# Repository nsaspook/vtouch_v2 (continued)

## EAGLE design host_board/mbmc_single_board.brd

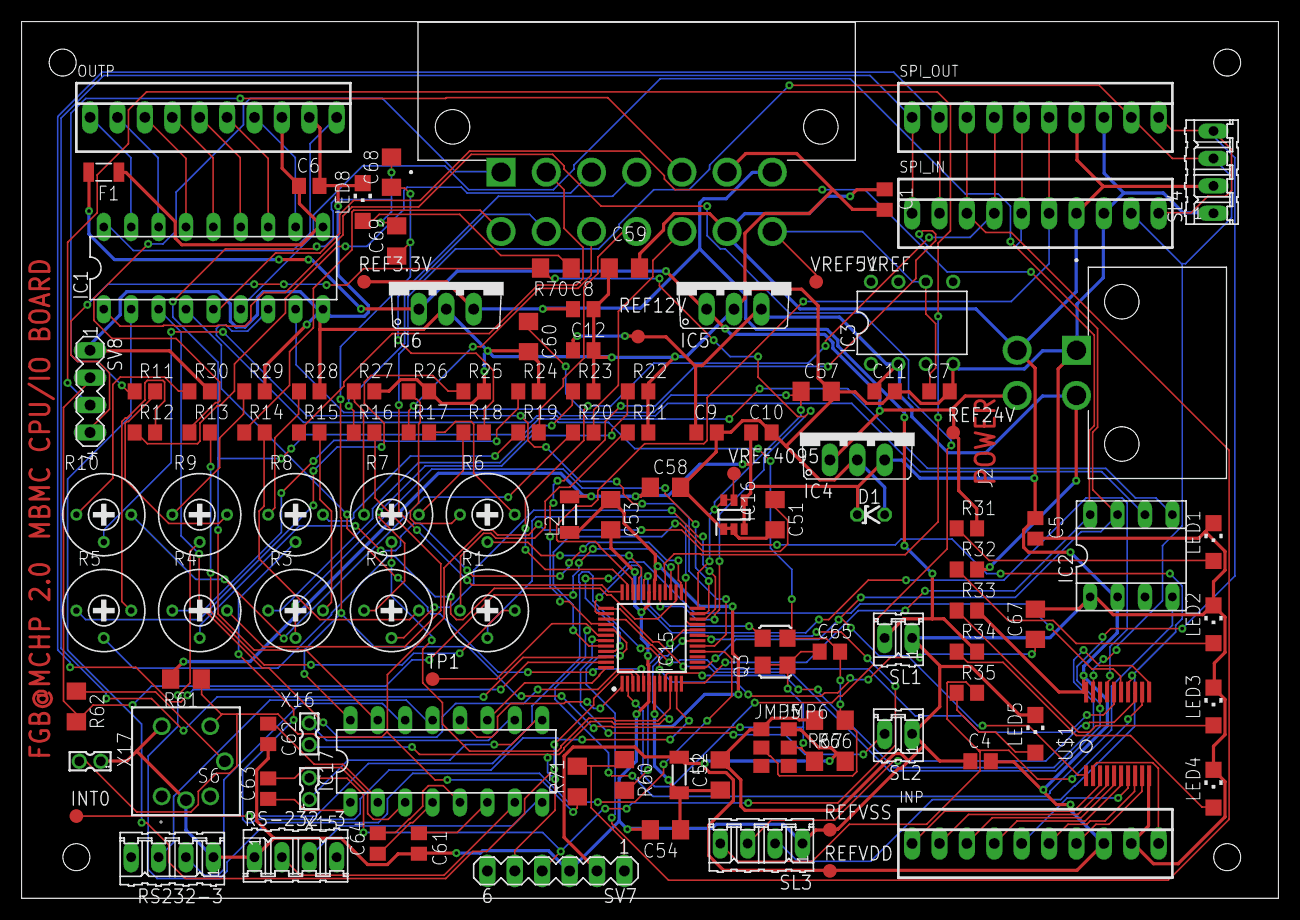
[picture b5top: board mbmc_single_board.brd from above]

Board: 2 copper layers, 116.5 x 81.3 mm, 118 parts (0 on the bottom side), 123 nets.

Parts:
C1, C12: 22uf; C0805
C4, C5, C6, C7, C8, C9, C10, C11: 0.1; C0805
C51, C52, C53, C57, C58, C67, C68, C69: 0.1; C1206
C54, C59, C60: 15uf; C1206
C61, C62, C63, C64, C65: 1uf; C0805
D1: 5.6v; ZDIO-2.5
F1: 1206L050; 1206L
IC1: ULN2803; DIL18
IC2: DIP Socket; SOCKET-08
IC3: REF02 5 VOLTS; DIL08
IC4: 5 VOLTS; TO220V
IC5: 12 VOLTS; TO220V
IC6: 3.3 VOLTS; TO220V
IC15: PIC18F57K42-E_PT; QFP50P900X900X120-48N
IC16: REF3440IDBVR; SOP95P280X145-6N
IC17: MAX232; DIL16
INP: 22-23-2101
INT0: TPB1,27; B1,27
J1: 1-1586043-4; TE_1-1586043-4
J2: 1586044-4; TE_1586044-4
JMP5, JMP6: 0R-JUMPA; A0R-JMP
L1, L2: 1000; SM-1206
LED1: 24 on; CHIPLED_1206
LED2: 12 on; CHIPLED_1206
LED3: 5 on; CHIPLED_1206
LED4: 3.3 on; CHIPLED_1206
LED5: debug8; CHIPLED_1206
LED8: DBLED; CHIPLED_1206
OUTP: 22-23-2101
Q3: ASF1; ASF
R1, R2, R3, R4, R5, R6, R7, R8, R9, R10: 200; RTRIM3339P
R11, R15, R16, R17, R18: 9.85k; R0805
R12, R20: 21.5k; R0805
R13, R14, R19: 811; R0805
R21, R22, R28: 3820; R0805
R23, R24, R25, R26, R27, R29, R30: 1.28k; R0805
R31: 10k; R0805
R32: 5k; R0805
R33, R34, R35: 1k; R0805
R60, R62, R70, R71: 220; R1206
R61: 10000; R1206
R66, R67: 0; R1206
REF3.3V, REF12V, REF24V: TPB1,27; B1,27
REFVDD: TPB1,27; B1,27
REFVSS: TPB1,27; B1,27
RS232-3: serial1; 04P
RS-232-3: serial2; 04P
S6: RESET SW; B3W-9_1-LED
SL1: 3.3 GLORY; 02P
SL2: PWM; 02P
SL3: MISC INP; 04P
SL4: SPI SEL; 04P
SPI_IN: 22-23-2101
SPI_OUT: 22-23-2101
SV7: ICSP; MA06-1
SV8: DEBUG; MA04-1
TP1: TPB1,27; B1,27
U$1: MAX6818; SSOP20
VREF5VREF, VREF4095: TPB1,27; B1,27
X15: RX-2; 332-02
X16: TX-2; 332-02
X17: RESETJMP; 332-02

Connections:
+3V3: C8.1, IC6.3, J1.13, R34.2, REF3.3V.TP, SL1.2
+12V: C9.1, C11.1, C12.1, IC3.2, IC5.3, J2.3, R32.2, REF12V.TP
+24V: F1.2, IC4.1, IC5.1, IC6.1, J2.4, R31.2, REF24V.TP
GND: C65.2, C68.2, C69.2, IC17.15, JMP5.2, Q3.2, R67.1
unnamed: R9.3, R11.2
unnamed: R5.3, R12.2
unnamed: R1.3, R13.2
unnamed: R2.3, R14.2
unnamed: R3.3, R15.2
unnamed: R4.3, R16.2
unnamed: R6.3, R17.2
unnamed: J1.7, R18.2
unnamed: R8.3, R19.1
unnamed: J1.8, R19.2
unnamed: R1.1, R21.1
unnamed: R2.1, R22.1
unnamed: R3.1, R23.1
unnamed: R4.1, R24.1
unnamed: R5.1, R25.1
unnamed: R6.1, R26.1
unnamed: R7.1, R27.1
unnamed: R8.1, R28.1
unnamed: R9.1, R29.1
unnamed: R10.1, R30.1
unnamed: C6.1, F1.1, IC1.10, OUTP.8
unnamed: C52.1, C53.1, C54.1, IC15.7, IC15.30, L1.2, L2.1
unnamed: J1.2, R14.1
unnamed: IC1.7, IC2.5
unnamed: IC1.8, IC2.6
unnamed: IC15.36, SL4.3, SPI_IN.9, SPI_OUT.9, U$1.OUT1
unnamed: INP.10, U$1.IN1
unnamed: INP.1, U$1.IN2
unnamed: INP.2, U$1.IN3
unnamed: INP.3, U$1.IN4
unnamed: INP.4, U$1.IN5
unnamed: INP.5, U$1.IN6
unnamed: INP.6, U$1.IN7
unnamed: INP.7, U$1.IN8
unnamed: IC1.18, OUTP.10
unnamed: IC1.17, OUTP.1
unnamed: IC1.16, OUTP.2
unnamed: IC1.15, OUTP.3
unnamed: IC1.14, OUTP.4
unnamed: IC1.13, OUTP.5
unnamed: IC1.12, OUTP.6
unnamed: IC1.11, OUTP.7
unnamed: C7.1, IC3.6, J1.14, VREF5VREF.TP
unnamed: IC15.46, SPI_IN.1, SPI_OUT.1
unnamed: J1.4, R16.1
unnamed: J1.9, R11.1
unnamed: J1.3, R15.1
unnamed: J1.10, R20.2
unnamed: J1.5, R12.1
unnamed: J1.6, R17.1
unnamed: J1.1, R13.1
unnamed: LED1.A, R31.1
unnamed: LED2.A, R32.1
unnamed: LED3.A, R33.1
unnamed: LED4.A, R34.1
unnamed: LED5.A, R35.1
unnamed: R35.2, SL3.4, U$1.OUT8
unnamed: R10.3, R20.1
unnamed: SL3.3, U$1.OUT7
unnamed: R7.3, R18.1
unnamed: IC17.8, RS-232-3.3
unnamed: IC17.14, RS232-3.2
unnamed: IC15.20, R60.2
unnamed: IC15.19, SV7.4, X15.2
unnamed: IC15.18, SV7.5, X16.2
unnamed: IC15.32, Q3.3
unnamed: C57.1, C60.1, IC15.24, IC16.5, IC16.6, VREF4095.TP
unnamed: C61.1, IC17.6
unnamed: C62.1, IC17.2
unnamed: C63.1, IC17.1
unnamed: C64.1, IC17.4
unnamed: C64.2, IC17.5
unnamed: C63.2, IC17.3
unnamed: IC17.7, RS-232-3.2
unnamed: IC17.13, RS232-3.3
unnamed: IC15.1, IC17.12
unnamed: IC17.9, X15.1
unnamed: IC15.48, IC17.11
unnamed: IC17.10, X16.1
unnamed: R62.1, S6.5
unnamed: IC15.27, R62.2, SV8.2
unnamed: IC15.28, SV8.3
unnamed: IC15.29, R70.2, SV8.4
unnamed: IC2.4, IC15.42, TP1.TP
unnamed: IC15.47, SPI_IN.2, SPI_OUT.2
unnamed: IC15.41, SPI_IN.3, SPI_OUT.3
unnamed: IC15.35, SPI_IN.4, SPI_OUT.4
unnamed: IC15.40, SPI_IN.5, SPI_OUT.5
unnamed: IC15.34, SPI_IN.6, SPI_OUT.6
unnamed: IC15.26, R5.2
unnamed: IC15.25, R4.2
unnamed: IC15.23, R3.2
unnamed: IC15.22, R2.2
unnamed: IC15.21, R1.2
unnamed: IC15.33, R6.2
unnamed: IC15.37, SL4.4, SPI_IN.10, SPI_OUT.10, U$1.OUT2
unnamed: IC15.44, SL3.2, U$1.OUT6
unnamed: IC15.45, U$1.OUT5
unnamed: IC1.1, IC15.2
unnamed: IC1.2, IC15.3
unnamed: IC1.3, IC15.4
unnamed: IC1.4, IC15.5
unnamed: IC15.38, U$1.OUT3
unnamed: IC15.39, U$1.OUT4
unnamed: IC15.43, SL2.2
unnamed: IC15.9, U$1.CH_L
unnamed: IC15.10, R7.2
unnamed: IC15.16, R9.2
unnamed: IC15.17, R10.2
unnamed: IC1.5, IC2.8, IC15.12
unnamed: IC1.6, IC2.7, IC15.13, U$1.EN_L
unnamed: IC15.11, R8.2
unnamed: C67.1, IC15.8, INT0.TP
unnamed: LED8.A, R70.1
unnamed: C51.1, R61.1, R71.1, S6.4, X17.2
unnamed: R60.1, R71.2, SV7.1
VCC: C65.1, C68.1, C69.1, IC17.16, JMP6.2, Q3.1, Q3.4, R66.1
VDD: C1.1, C4.2, C5.1, C10.1, C58.1, C59.1, D1.C, IC2.2, IC4.3, IC16.3, IC16.4, INP.8, J1.12, J2.2, JMP6.1, L1.1, L2.2, R33.2, R61.2, R66.2, REFVDD.TP, SL4.2, SPI_IN.7, SPI_OUT.7, SV7.2, U$1.VCC
VSS: C1.2, C4.1, C5.2, C6.2, C7.2, C8.2, C9.2, C10.2, C11.2, C12.2, C51.2, C52.2, C53.2, C54.2, C57.2, C58.2, C59.2, C60.2, C61.2, C62.2, C67.2, D1.A, IC1.9, IC2.1, IC3.4, IC4.2, IC5.2, IC6.2, IC15.6, IC15.31, IC16.1, IC16.2, INP.9, J1.11, J2.1, JMP5.1, LED1.C, LED2.C, LED3.C, LED4.C, LED5.C, LED8.C, OUTP.9, R21.2, R22.2, R23.2, R24.2, R25.2, R26.2, R27.2, R28.2, R29.2, R30.2, R67.2, REFVSS.TP, RS232-3.1, RS-232-3.1, S6.2, S6.6, SL1.1, SL2.1, SL3.1, SL4.1, SPI_IN.8, SPI_OUT.8, SV7.3, SV8.1, U$1.GND, X17.1

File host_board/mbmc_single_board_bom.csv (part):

"Part";"Value";"Device";"Package";"Description";"ALLIED_NUMBER";"ALLIED_PRICE-STOCK";"AVAILABILITY";"DESCRIPTION";"HEIGHT";"MANUFACTURER";"MANUFACTURER_NAME";"MANUFACTURER_PART_NUMBER";"MF";"MOUSER_PART_NUMBER";"MOUSER_PRICE-STOCK";"MP";"MPN";"OC_FARNELL";"OC_NEWARK";"PACKAGE";"PARTREV";"POPULARITY";"PRICE";"RS_PART_NUMBER";"RS_PRICE-STOCK";"SPICEMODEL";"SPICEPREFIX";"SPICEPREFIXL";"STANDARD";"TP_SIGNAL_NAME";
"C1";"22uf";"C-USC0805";"C0805";"CAPACITOR, American symbol";"";"";"";"";"";"";"";"";"";"";"";"";"";"";"";"";"";"";"";"";"";"";"C";"";"";"";
"C4";"0.1";"C-USC0805";"C0805";"CAPACITOR, American symbol";"";"";"";"";"";"";"";"";"";"";"";"";"";"";"";"";"";"";"";"";"";"";"C";"";"";"";
"C5";"0.1";"C-USC0805";"C0805";"CAPACITOR, American symbol";"";"";"";"";"";"";"";"";"";"";"";"";"";"";"";"";"";"";"";"";"";"";"C";"";"";"";
"C6";"0.1";"C-USC0805";"C0805";"CAPACITOR, American symbol";"";"";"";"";"";"";"";"";"";"";"";"";"";"";"";"";"";"";"";"";"";"";"C";"";"";"";
"C7";"0.1";"C-USC0805";"C0805";"CAPACITOR, American symbol";"";"";"";"";"";"";"";"";"";"";"";"";"";"";"";"";"";"";"";"";"";"";"C";"";"";"";
"C8";"0.1";"C-USC0805";"C0805";"CAPACITOR, American symbol";"";"";"";"";"";"";"";"";"";"";"";"";"";"";"";"";"";"";"";"";"";"";"C";"";"";"";
"C9";"0.1";"C-USC0805";"C0805";"CAPACITOR, American symbol";"";"";"";"";"";"";"";"";"";"";"";"";"";"";"";"";"";"";"";"";"";"";"C";"";"";"";
"C10";"0.1";"C-USC0805";"C0805";"CAPACITOR, American symbol";"";"";"";"";"";"";"";"";"";"";"";"";"";"";"";"";"";"";"";"";"";"";"C";"";"";"";
"C11";"0.1";"C-USC0805";"C0805";"CAPACITOR, American symbol";"";"";"";"";"";"";"";"";"";"";"";"";"";"";"";"";"";"";"";"";"";"";"C";"";"";"";
"C12";"22uf";"C-USC0805";"C0805";"CAPACITOR, American symbol";"";"";"";"";"";"";"";"";"";"";"";"";"";"";"";"";"";"";"";"";"";"";"C";"";"";"";
"C51";"0.1";"C-USC1206";"C1206";"CAPACITOR, American symbol";"";"";"";"";"";"";"";"";"";"";"";"";"";"";"";"";"";"";"";"";"";"";"C";"";"";"";
"C52";"0.1";"C-USC1206";"C1206";"CAPACITOR, American symbol";"";"";"";"";"";"";"";"";"";"";"";"";"";"";"";"";"";"";"";"";"";"";"C";"";"";"";
"C53";"0.1";"C-USC1206";"C1206";"CAPACITOR, American symbol";"";"";"";"";"";"";"";"";"";"";"";"";"";"";"";"";"";"";"";"";"";"";"C";"";"";"";
"C54";"15uf";"C-USC1206";"C1206";"CAPACITOR, American symbol";"";"";"";"";"";"";"";"";"";"";"";"";"";"";"";"";"";"";"";"";"";"";"C";"";"";"";
"C57";"0.1";"C-USC1206";"C1206";"CAPACITOR, American symbol";"";"";"";"";"";"";"";"";"";"";"";"";"";"";"";"";"";"";"";"";"";"";"C";"";"";"";
"C58";"0.1";"C-USC1206";"C1206";"CAPACITOR, American symbol";"";"";"";"";"";"";"";"";"";"";"";"";"";"";"";"";"";"";"";"";"";"";"C";"";"";"";
"C59";"15uf";"C-USC1206";"C1206";"CAPACITOR, American symbol";"";"";"";"";"";"";"";"";"";"";"";"";"";"";"";"";"";"";"";"";"";"";"C";"";"";"";
"C60";"15uf";"C-USC1206";"C1206";"CAPACITOR, American symbol";"";"";"";"";"";"";"";"";"";"";"";"";"";"";"";"";"";"";"";"";"";"";"C";"";"";"";
"C61";"1uf";"C-USC0805";"C0805";"CAPACITOR, American symbol";"";"";"";"";"";"";"";"";"";"";"";"";"";"";"";"";"";"";"";"";"";"";"C";"";"";"";
"C62";"1uf";"C-USC0805";"C0805";"CAPACITOR, American symbol";"";"";"";"";"";"";"";"";"";"";"";"";"";"";"";"";"";"";"";"";"";"";"C";"";"";"";
"C63";"1uf";"C-USC0805";"C0805";"CAPACITOR, American symbol";"";"";"";"";"";"";"";"";"";"";"";"";"";"";"";"";"";"";"";"";"";"";"C";"";"";"";
"C64";"1uf";"C-USC0805";"C0805";"CAPACITOR, American symbol";"";"";"";"";"";"";"";"";"";"";"";"";"";"";"";"";"";"";"";"";"";"";"C";"";"";"";
"C65";"1uf";"C-USC0805";"C0805";"CAPACITOR, American symbol";"";"";"";"";"";"";"";"";"";"";"";"";"";"";"";"";"";"";"";"";"";"";"C";"";"";"";
"C67";"0.1";"C-USC1206";"C1206";"CAPACITOR, American symbol";"";"";"";"";"";"";"";"";"";"";"";"";"";"";"";"";"";"";"";"";"";"";"C";"";"";"";
"C68";"0.1";"C-USC1206";"C1206";"CAPACITOR, American symbol";"";"";"";"";"";"";"";"";"";"";"";"";"";"";"";"";"";"";"";"";"";"";"C";"";"";"";
"C69";"0.1";"C-USC1206";"C1206";"CAPACITOR, American symbol";"";"";"";"";"";"";"";"";"";"";"";"";"";"";"";"";"";"";"";"";"";"";"C";"";"";"";
"D1";"5.6v";"ZENER-DIODEZD-2.5";"ZDIO-2.5";"Z-Diode";"";"";"";"";"";"";"";"";"";"";"";"";"";"";"";"";"";"4";"";"";"";"";"";"";"";"";
"F1";"1206L050";"1206L050";"1206L";"Polyfuse Resettable PTC";"";"";"";"";"";"";"";"";"Littelfuse";"";"";"";"1206L050";"1596993";"53M6118";"";"";"";"";"";"";"";"";"";"";"";
"IC1";"ULN2803";"ULN2803A";"DIL18";"DRIVER ARRAY";"";"";"";"";"";"";"";"";"";"";"";"";"";"";"";"";"";"5";"";"";"";"";"";"";"";"";
"IC2";"DIP Socket";"DIL8S";"SOCKET-08";"Dual In Line / Socket";"";"";"";"";"";"";"";"";"";"";"";"";"";"";"";"";"";"";"";"";"";"";"";"";"";"";
"IC3";"REF02 5 VOLTS";"REF02Z";"DIL08";"VOLTAGE REFERENCE";"";"";"";"";"";"";"";"";"";"";"";"";"";"";"";"";"";"0";"";"";"";"";"";"";"";"";
"IC4";"5 VOLTS";"7805TV";"TO220V";"Positive VOLTAGE REGULATOR";"";"";"";"";"";"";"";"";"";"";"";"";"";"";"";"";"";"57";"";"";"";"";"";"";"";"";
"IC5";"12 VOLTS";"7805TV";"TO220V";"Positive VOLTAGE REGULATOR";"";"";"";"";"";"";"";"";"";"";"";"";"";"";"";"";"";"57";"";"";"";"";"";"";"";"";
"IC6";"3.3 VOLTS";"7805TV";"TO220V";"Positive VOLTAGE REGULATOR";"";"";"";"";"";"";"";"";"";"";"";"";"";"";"";"";"";"57";"";"";"";"";"";"";"";"";
"IC15";"PIC18F57K42-E_PT";"PIC18F57K42-E_PT";"QFP50P900X900X120-48N";"8-bit Microcontrollers - MCU 128KB Flash, 8KB RAM, 256B EEPROM, 12-bit ADC2, Vector Interrupts, DMA, MAP, DIA, DAC, Comp, PWM, CWG, HLT, WWDT, SCAN/CRC, ZCD, PPS, EUSART, SPI/I2C, IDLE/DOZE/PMD";"";"";"";"8-bit Microcontrollers - MCU 128KB Flash, 8KB RAM, 256B EEPROM, 12-bit ADC2, Vector Interrupts, DMA, MAP, DIA, DAC, Comp, PWM, CWG, HLT, WWDT, SCAN/CRC, ZCD, PPS, EUSART, SPI/I2C, IDLE/DOZE/PMD";"1.2mm";"";"Microchip";"PIC18F57K42-E/PT";"";"579-PIC18F57K42-E/PT";"";"";"";"";"";"";"";"";"";"";"";"";"";"";"";"";
"IC16";"REF3440IDBVR";"REF3440IDBVR";"SOP95P280X145-6N";"4.1V Low-Drift Low-Power Small-Footprint Series Voltage Reference";"";"";"";"4.1V Low-Drift Low-Power Small-Footprint Series Voltage Reference";"1.45mm";"";"Texas Instruments";"REF3440IDBVR";"";"";"";"";"";"";"";"";"";"";"";"";"";"";"";"";"";"";
"IC17";"MAX232";"MAX232";"DIL16";"RS232 TRANSCEIVER";"";"";"";"";"";"";"";"";"MAXIM";"";"";"";"MAX232ACPE+";"9723773";"68K4544";"";"";"";"";"";"";"";"";"";"";"";
"INP";"22-23-2101";"22-23-2101";"22-23-2101";".100" (2.54mm) Center Header - 10 Pin";"";"";"";"";"";"";"";"";"MOLEX";"";"";"";"22-23-2101";"1756828";"94C0765";"";"";"";"";"";"";"";"";"";"";"";
"INT0";"TPB1,27";"TPB1,27";"B1,27";"Test pad";"";"";"";"";"";"";"";"";"";"";"";"";"";"";"";"";"";"19";"";"";"";"";"";"";"";"";
"J1";"1-1586043-4";"1-1586043-4";"TE_1-1586043-4";"";"";"";"";"";"";"TE";"";"";"";"";"";"";"";"";"";"";"R";"";"";"";"";"";"";"";"Manufacturer Recommendations";"";
"J2";"1586044-4";"1586044-4";"TE_1586044-4";"";"";"";"";"";"";"TE";"";"";"";"";"";"";"";"";"";"";"R";"";"";"";"";"";"";"";"Manufacturer Recommendations";"";
"JMP5";"0R-JUMPA";"0R-JUMPA";"A0R-JMP";"SMD 0R 0805 Jumper";"";"";"";"";"";"";"";"";"";"";"";"";"";"";"";"";"";"";"";"";"";"";"";"";"";"";
"JMP6";"0R-JUMPA";"0R-JUMPA";"A0R-JMP";"SMD 0R 0805 Jumper";"";"";"";"";"";"";"";"";"";"";"";"";"";"";"";"";"";"";"";"";"";"";"";"";"";"";
"L1";"1000";"SM-1206";"SM-1206";"INDUCTOR";"";"";"";"";"";"";"";"";"";"";"";"";"";"unknown";"unknown";"";"";"0";"";"";"";"";"";"";"";"";
"L2";"1000";"SM-1206";"SM-1206";"INDUCTOR";"";"";"";"";"";"";"";"";"";"";"";"";"";"unknown";"unknown";"";"";"0";"";"";"";"";"";"";"";"";
"LED1";"24 on";"LEDCHIPLED_1206";"CHIPLED_1206";"LED";"";"";"";"";"";"";"";"";"";"";"";"";"";"";"";"";"";"";"";"";"";"";"";"";"";"";
"LED2";"12 on";"LEDCHIPLED_1206";"CHIPLED_1206";"LED";"";"";"";"";"";"";"";"";"";"";"";"";"";"";"";"";"";"";"";"";"";"";"";"";"";"";
"LED3";"5 on";"LEDCHIPLED_1206";"CHIPLED_1206";"LED";"";"";"";"";"";"";"";"";"";"";"";"";"";"";"";"";"";"";"";"";"";"";"";"";"";"";
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
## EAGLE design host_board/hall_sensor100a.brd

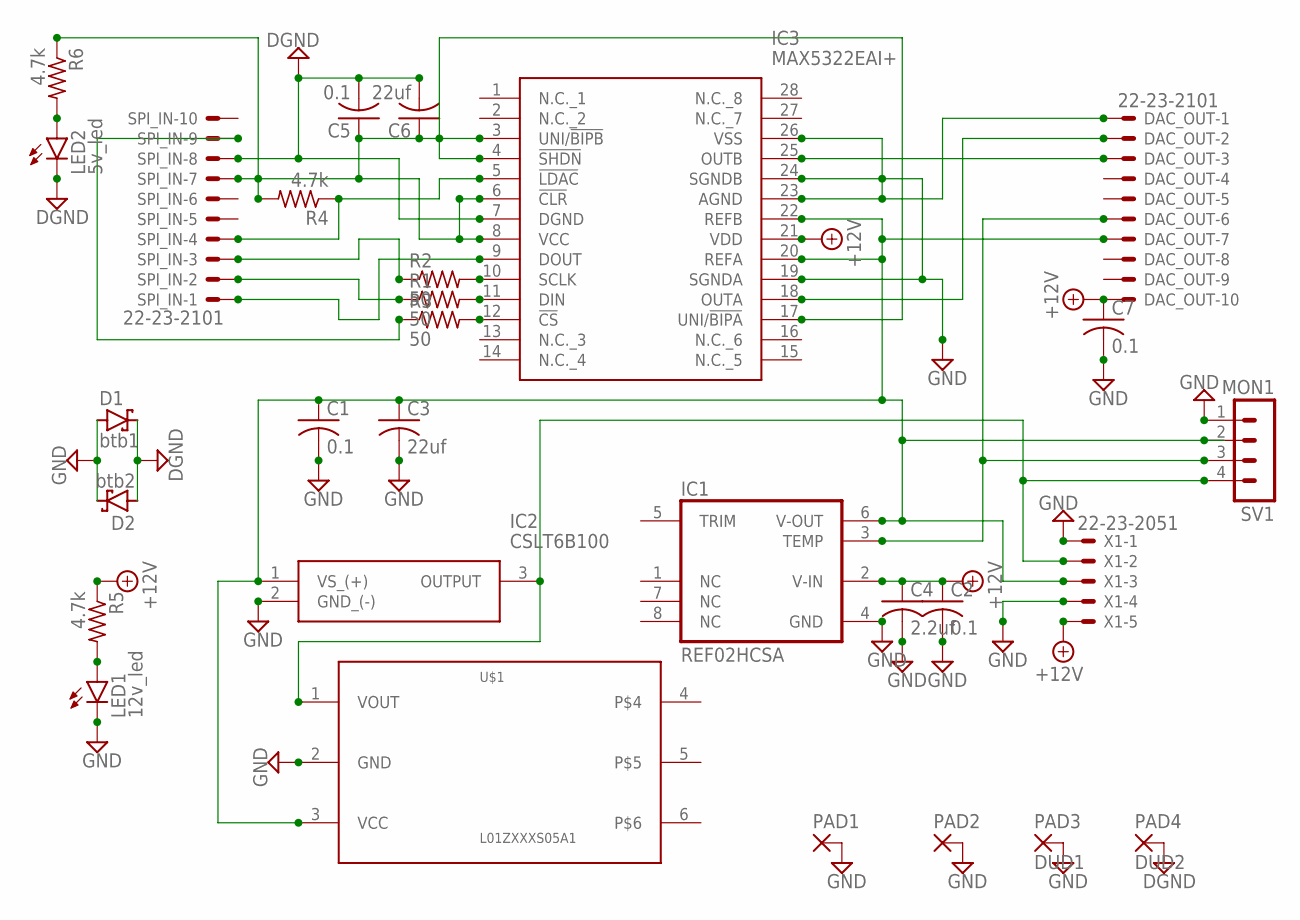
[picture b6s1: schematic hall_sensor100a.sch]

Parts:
C1, C2, C5, C7: 0.1; C0805
C3, C6: 22uf; C0805
C4: 2.2uf; C0805
D1: btb1; DO35-7
D2: btb2; DO35-7
DAC_OUT: 22-23-2101
IC1: REF02HCSA; SO08
IC2: CSLT6B100
IC3: MAX5322EAI+; SOP65P778X199-28N
LED1: 12v_led; CHIPLED_1206
LED2: 5v_led; CHIPLED_1206
PAD1, PAD2: 2,15/1,0
PAD3: DUD1; 2,15/1,0
PAD4: DUD2; 2,15/1,0
R1, R2, R3: 50; M0805
R4, R5, R6: 4.7k; M0805
SPI_IN: 22-23-2101
SV1: MON1; MA04-1
U$1: L01ZXXXS05A1; DIP2540W53P254L2900H508Q6B
X1: 22-23-2051

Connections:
+12V: C2.1, C4.1, C7.1, DAC_OUT.10, IC1.2 (V-IN), IC3.21 (VDD), R5.1, X1.5
DGND: C5.2, C6.2, D1.C, D2.A, IC3.7 (DGND), LED2.C, PAD4.1, SPI_IN.8
GND: C1.2, C2.2, C3.2, C4.2, C7.2, D1.A, D2.C, DAC_OUT.1, IC1.4 (GND), IC2.2 (GND_(-)), IC3.19 (SGNDA), IC3.23 (AGND), IC3.24 (SGNDB), IC3.26 (VSS), LED1.C, PAD1.1, PAD2.1, PAD3.1, SV1.1, U$1.2 (GND), X1.1, X1.4
unnamed: C1.1, C3.1, DAC_OUT.7, IC1.6 (V-OUT), IC2.1 (VS_(+)), IC3.20 (REFA), IC3.22 (REFB), SV1.2, U$1.3 (VCC), X1.3
unnamed: IC2.3 (OUTPUT), SV1.4, U$1.1 (VOUT), X1.2
unnamed: IC3.11 (DIN), R1.2
unnamed: DAC_OUT.2, IC3.18 (OUTA)
unnamed: DAC_OUT.3, IC3.25 (OUTB)
unnamed: R1.1, SPI_IN.2
unnamed: IC3.9 (DOUT), SPI_IN.1
unnamed: R2.1, SPI_IN.3
unnamed: R3.1, SPI_IN.9
unnamed: C5.1, C6.1, IC3.3 (UNI/!BIPB), IC3.4 (!SHDN), IC3.6 (!CLR), IC3.8 (VCC), IC3.17 (UNI/!BIPA), R4.2, R6.1, SPI_IN.7
unnamed: LED1.A, R5.2
unnamed: IC3.5 (!LDAC), R4.1, SPI_IN.4
unnamed: IC3.10 (SCLK), R2.2
unnamed: IC3.12 (!CS), R3.2
unnamed: DAC_OUT.6, IC1.3 (TEMP), SV1.3
unnamed: LED2.A, R6.2

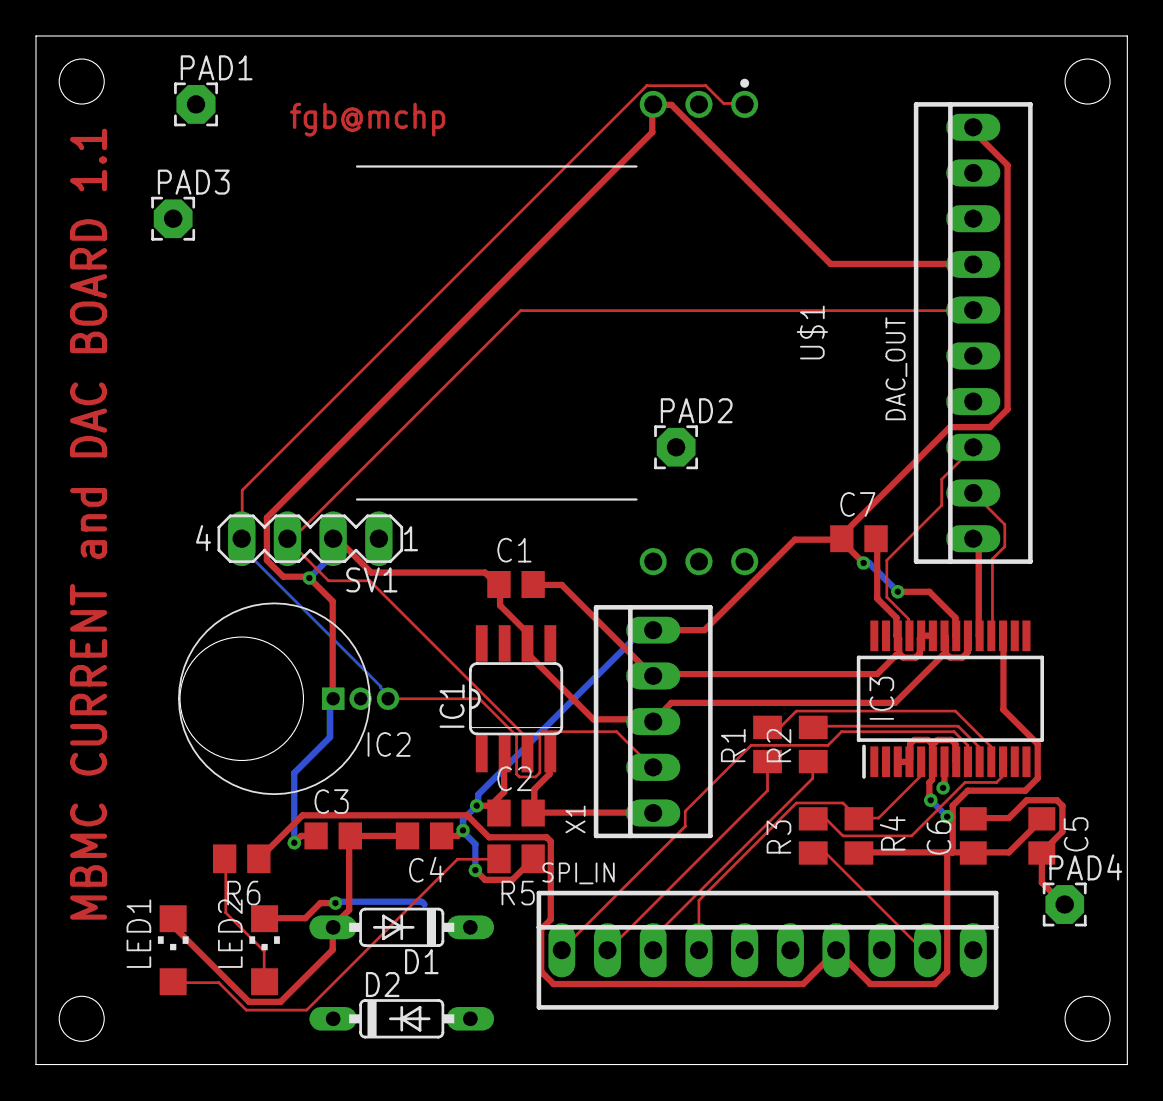
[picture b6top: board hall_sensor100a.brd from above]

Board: 2 copper layers, 60.6 x 57.1 mm, 29 parts (0 on the bottom side), 19 nets.

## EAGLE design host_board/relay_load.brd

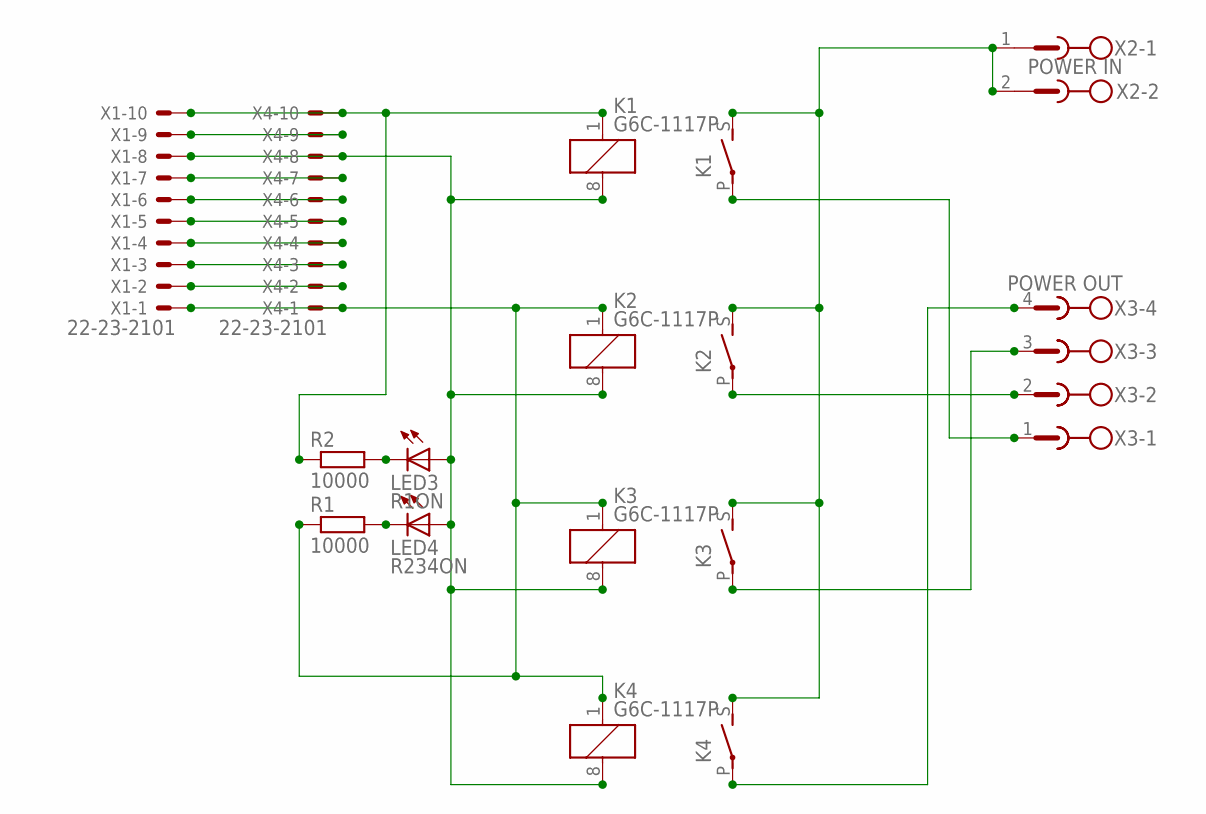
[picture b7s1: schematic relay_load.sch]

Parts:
K1, K2, K3, K4: G6C-1117P
LED3: R1ON; LED_1206
LED4: R234ON; LED_1206
R1, R2: 10000; R1206
X1, X4: 22-23-2101
X2: POWER IN; MSTBV2
X3: POWER OUT; MSTBV4

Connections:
unnamed: K1.S, K2.S, K3.S, K4.S, X2.1, X2.2
unnamed: K1.8 (2), K2.8 (2), K3.8 (2), K4.8 (2), LED3.A, LED4.A, X1.8, X4.8
unnamed: K1.1, R2.1, X1.10, X4.10
unnamed: K2.1, K3.1, K4.1, R1.1, X1.1, X4.1
unnamed: X1.9, X4.9
unnamed: X1.7, X4.7
unnamed: K1.P, X3.1
unnamed: K2.P, X3.2
unnamed: K3.P, X3.3
unnamed: K4.P, X3.4
unnamed: X1.6, X4.6
unnamed: X1.5, X4.5
unnamed: X1.4, X4.4
unnamed: X1.3, X4.3
unnamed: X1.2, X4.2
unnamed: LED4.C, R1.2
unnamed: LED3.C, R2.2

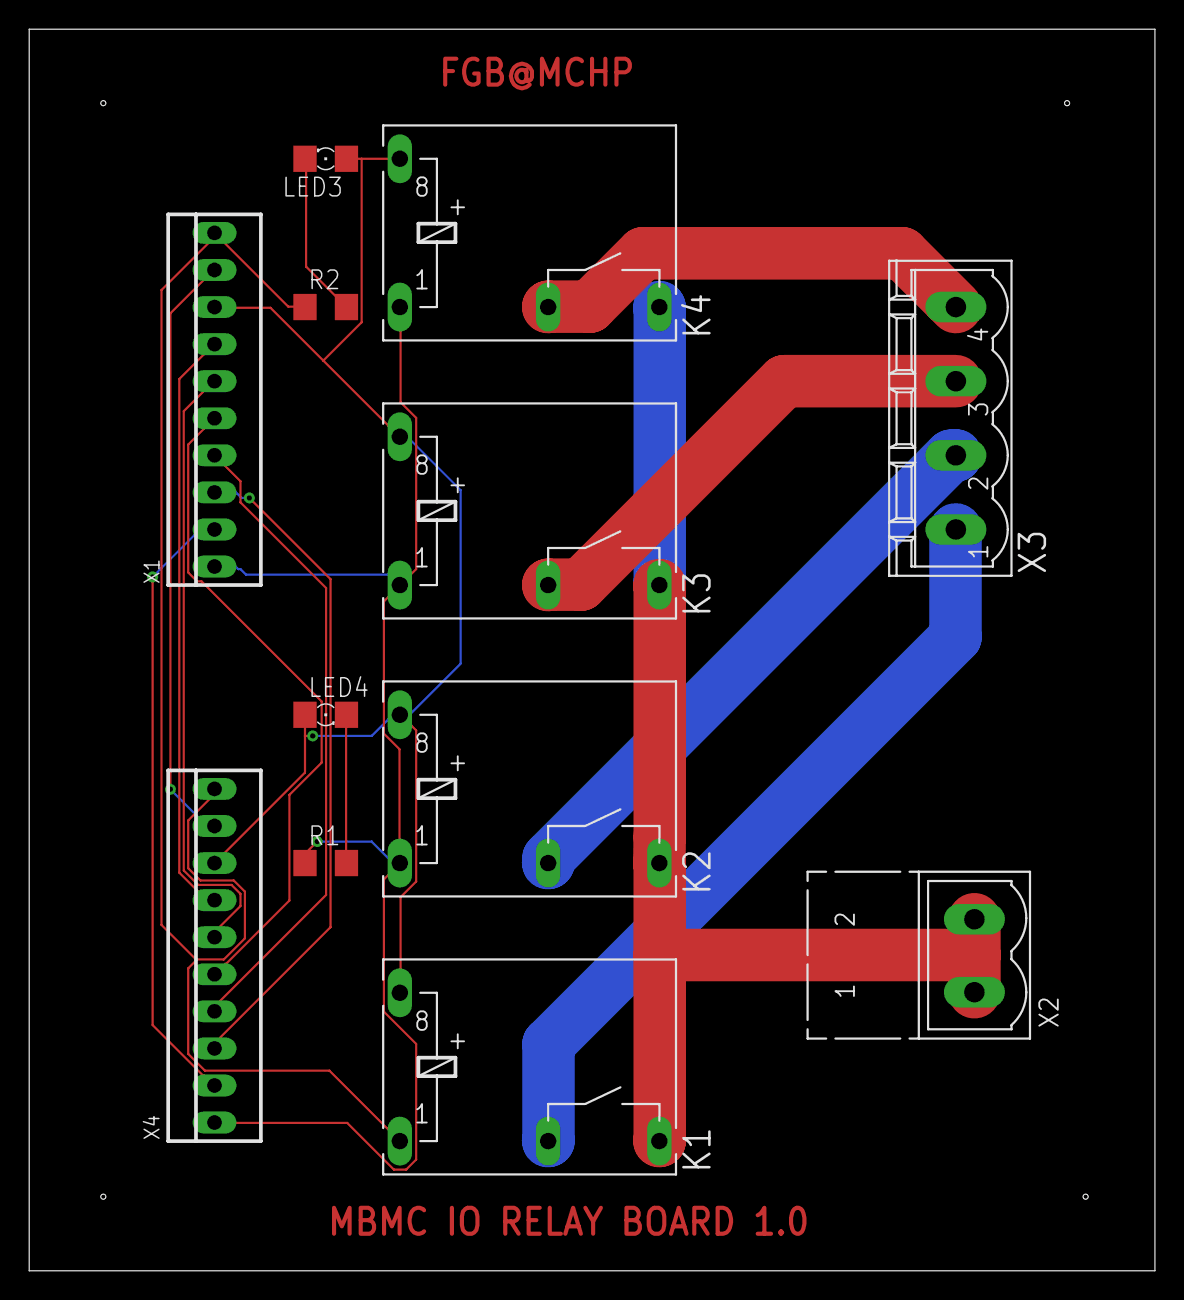
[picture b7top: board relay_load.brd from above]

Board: 2 copper layers, 77.1 x 85.1 mm, 12 parts (0 on the bottom side), 17 nets.

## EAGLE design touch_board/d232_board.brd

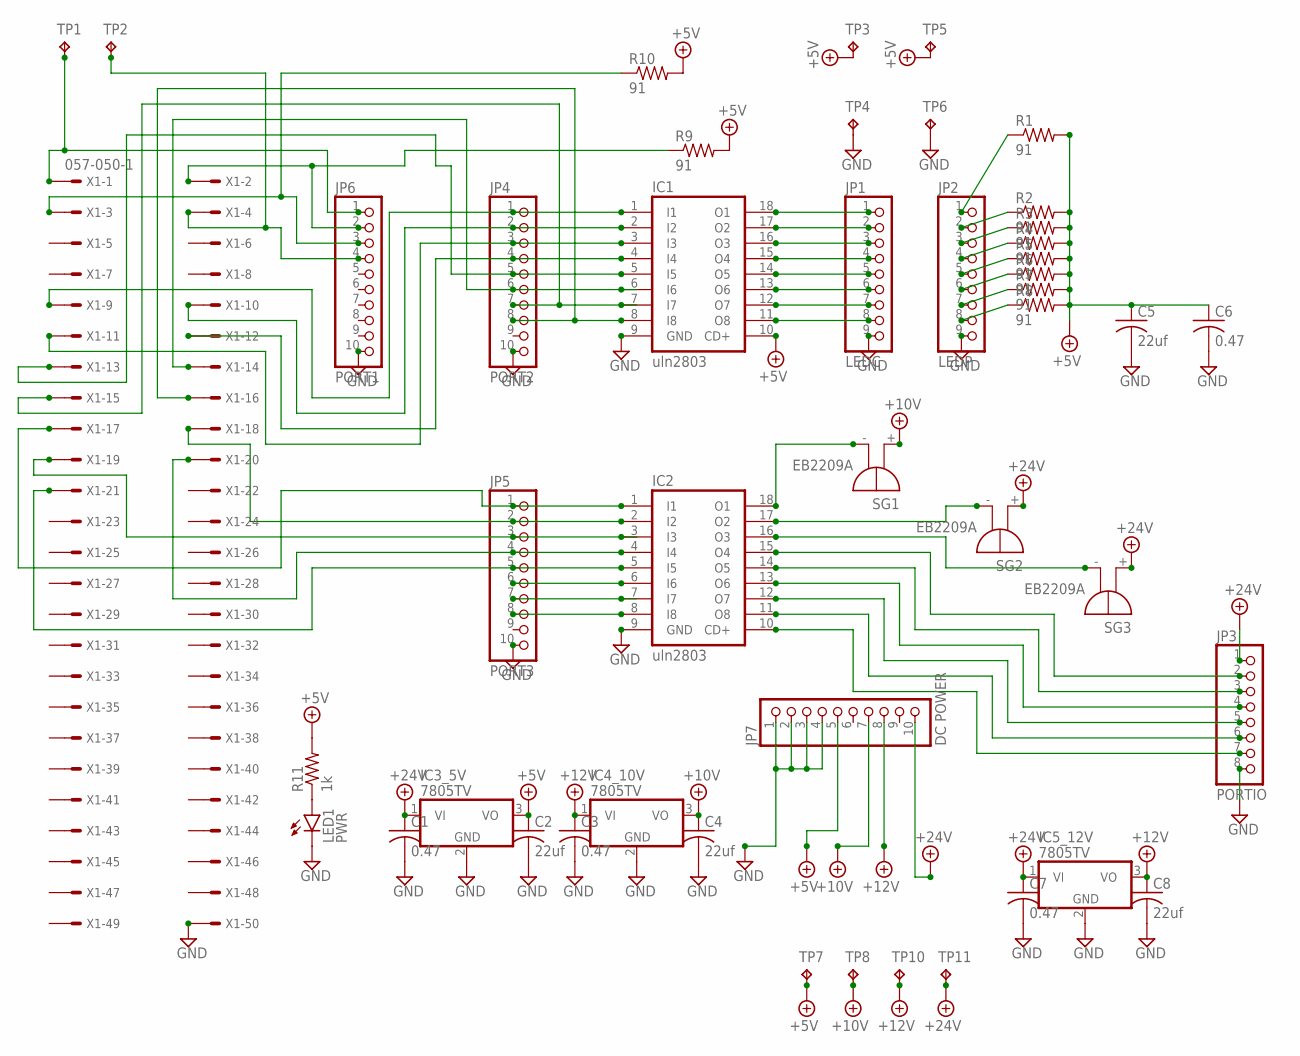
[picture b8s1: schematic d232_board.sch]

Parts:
C1, C3, C6, C7: 0.47; C1206K
C2, C4, C5, C8: 22uf; C1206K
IC1, IC2: uln2803; DIL18
IC3_5V, IC4_10V, IC5_12V: 7805TV; TO220V
JP1: LEDC; 1X09
JP2: LEDP; 1X09
JP3: PORTIO; 1X08
JP4: PORT2; 1X10
JP5: PORT3; 1X10
JP6: PORT1; 1X10
JP7: DC POWER; 1X10
LED1: PWR; CHIPLED_1206
R1, R2, R3, R4, R5, R6, R7, R8, R9, R10: 91; 0204V
R11: 1k; 0204V
SG1, SG2, SG3: EB2209A
TP1, TP2, TP3, TP4, TP5, TP6, TP7, TP8, TP10, TP11: TPB2,54; B2,54
X1: 057-050-1

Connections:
+5V: C2.1, C5.1, C6.1, IC1.10 (CD+), IC3_5V.3 (VO), JP7.5, R1.2, R2.2, R3.2, R4.2, R5.2, R6.2, R7.2, R8.2, R9.2, R10.2, R11.2, TP3.TP, TP5.TP, TP7.TP
+10V: C4.1, IC4_10V.3 (VO), JP7.7, SG1.+, TP8.TP
+12V: C3.1, C8.1, IC4_10V.1 (VI), IC5_12V.3 (VO), JP7.8, TP10.TP
+24V: C1.1, C7.1, IC3_5V.1 (VI), IC5_12V.1 (VI), JP3.1, JP7.10, SG2.+, SG3.+, TP11.TP
GND: C1.2, C2.2, C3.2, C4.2, C5.2, C6.2, C7.2, C8.2, IC1.9 (GND), IC2.9 (GND), IC3_5V.2 (GND), IC4_10V.2 (GND), IC5_12V.2 (GND), JP1.9, JP2.9, JP3.8, JP4.10, JP5.10, JP6.10, JP7.1, JP7.2, JP7.3, JP7.4, LED1.C, TP4.TP, TP6.TP, X1.50
unnamed: IC1.18 (O1), JP1.1
unnamed: IC1.17 (O2), JP1.2
unnamed: IC1.16 (O3), JP1.3
unnamed: IC1.15 (O4), JP1.4
unnamed: IC1.14 (O5), JP1.5
unnamed: IC1.13 (O6), JP1.6
unnamed: IC1.12 (O7), JP1.7
unnamed: IC1.11 (O8), JP1.8
unnamed: IC1.1 (I1), JP4.1, X1.9
unnamed: IC1.2 (I2), JP4.2, X1.10
unnamed: IC1.3 (I3), JP4.3, X1.11
unnamed: IC1.4 (I4), JP4.4, X1.12
unnamed: IC1.5 (I5), JP4.5, X1.13
unnamed: IC1.6 (I6), JP4.6, X1.14
unnamed: IC1.7 (I7), JP4.7, X1.15
unnamed: IC1.8 (I8), JP4.8, X1.16
unnamed: IC2.1 (I1), JP5.1, X1.17
unnamed: IC2.2 (I2), JP5.2, X1.18
unnamed: IC2.3 (I3), JP5.3, X1.19
unnamed: IC2.4 (I4), JP5.4, X1.20
unnamed: IC2.5 (I5), JP5.5, X1.21
unnamed: IC2.6 (I6), JP5.6
unnamed: IC2.7 (I7), JP5.7
unnamed: IC2.8 (I8), JP5.8
unnamed: IC2.18 (O1), SG1.-
unnamed: IC2.17 (O2), SG2.-
unnamed: IC2.16 (O3), SG3.-
unnamed: JP6.1, TP1.TP, X1.1
unnamed: JP6.2, R9.1, X1.2
unnamed: JP6.3, R10.1, X1.3
unnamed: JP6.4, TP2.TP, X1.4
unnamed: JP2.1, R1.1
unnamed: JP2.2, R2.1
unnamed: JP2.3, R3.1
unnamed: JP2.4, R4.1
unnamed: JP2.5, R5.1
unnamed: JP2.6, R6.1
unnamed: JP2.7, R7.1
unnamed: JP2.8, R8.1
unnamed: IC2.15 (O4), JP3.2
unnamed: IC2.14 (O5), JP3.3
unnamed: IC2.13 (O6), JP3.4
unnamed: IC2.12 (O7), JP3.5
unnamed: IC2.11 (O8), JP3.6
unnamed: IC2.10 (CD+), JP3.7
unnamed: LED1.A, R11.1

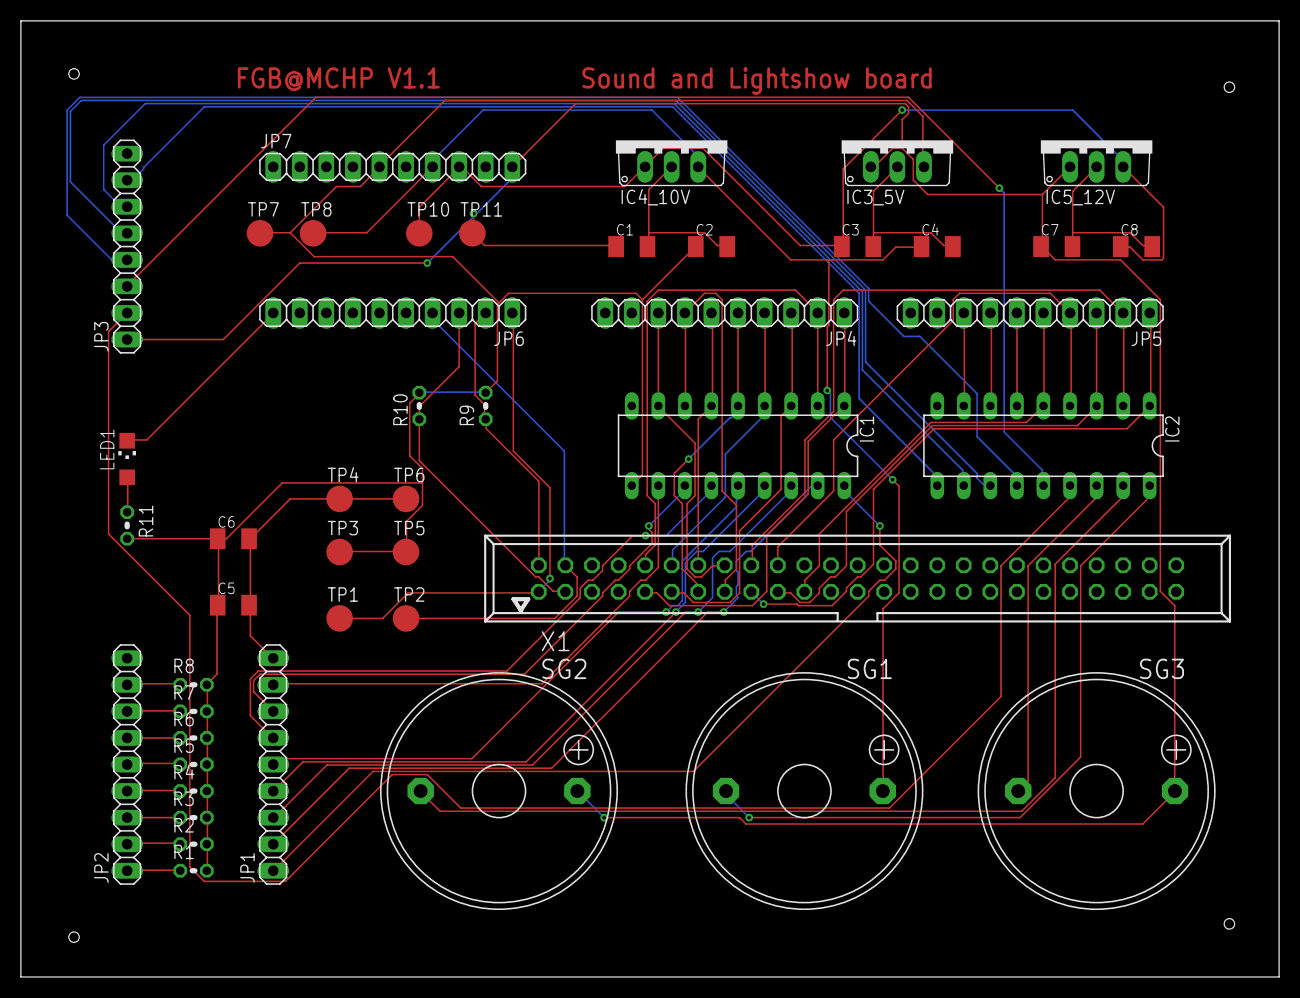
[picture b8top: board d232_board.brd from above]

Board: 2 copper layers, 120.3 x 91.4 mm, 46 parts (0 on the bottom side), 51 nets.

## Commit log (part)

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2020-04-06 up:wq
2024-12-17 secs
2024-12-17 update SECS
2024-12-17 update to secs_gem
2025-02-13 two layer board
2025-02-15 messeges
2025-02-22 terminal message cleanups
